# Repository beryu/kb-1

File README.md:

# komoro

komoroは、19mmトラックボールを搭載した左右分割キーボードです。

コンパクトな17mmピッチのカラムスタッカード配列を採用し、左右合わせて48キーを搭載しています。
トラックボールの高さを低く抑えることで、キーを打つときや持ち運びの邪魔になりにくくしています。
コントローラーにはSeeed Studio XIAO nRF52840 Plusを採用しています。XIAOは右側だけに搭載し、左右間はSamtec FTSHヘッダとFFSD-06-D-10.00-01-Nケーブルで接続します。PCとはBluetoothで通信しますが、動作中は右側USB-Cから常に給電する必要があります。

| 左側PCB | 右側PCB |
| --- | --- |
|  |  |

※画像は旧リビジョンの基板です。現行のコネクタや部品配置は[`pcb/`の製造用PCBデータ](pcb/)を確認してください。

## [ビルドガイド](build-guide.md)

## 特徴

* 17mmピッチのカラムスタッカード配列
  * 左26キー、右22キーの48キー構成です。
* USB-C給電・Bluetooth接続
  * PCとの通信にはBluetoothを使用します。
  * 使用中は右側XIAOへモバイルバッテリーまたはUSB電源から常に給電する必要があります。
  * 電源スイッチはなく、USB-Cケーブルの接続／取り外しで電源を操作します。
  * 左右間は、Samtec FFSD-06-D-10.00-01-Nケーブルで接続します。
* Seeed Studio XIAO nRF52840 Plusを採用
  * XIAOは右側だけに搭載し、左側はコントローラーを持たない受動基板です。
* トラックボールの設置位置が調整可能
  * トラックボールを取り付ける位置を調整して、自分にとって一番操作しやすい位置に設置できます。ボールの高さを抑えたことでキーを打つときの邪魔になりにくくなっています。
* ZMK対応
  * [komoro専用ファームウェア](https://github.com/beryu/zmk-keyboard-kb-1)を公開しています。
  * keymap-editorやZMK Studioを使用して簡単にキーマップが変更できます。

## 使用上の注意

* 異臭や煙が出たときは、ただちにUSB-C電源を外して使用を中止してください。
* 左右を接続するFFSDケーブルは、USB-C電源を外した状態で抜き差ししてください。
* USB-C電源とケーブルは、破損や発熱のない適合品を使用してください。

## 設計データについて

本リポジトリでは、komoroの基板設計データと19mmトラックボールケースの設計データを公開しています。

19mmトラックボールケースには、PAW3222センサーモジュールのズレを抑える[ガイド追加版STL](3d-models/STL/trackball-case-19mm-ortho-sensor-fit-Body.stl)を用意しています。寸法と印刷・再生成方法は[センサー溝の調整説明](3d-models/FreeCAD/TRACKBALL-SENSOR-FIT.md)を確認してください。再生成の入力に使う従来版STLは残し、旧トラックボールケースのFreeCADファイルは削除しています。本体ケースのFreeCADデータとSTLは現行PCB外形、左右上面のFFSDコネクタ、右側USB-Cに合わせて更新しています。印刷前に実部品との干渉を確認してください。

ライセンスにしたがって自由に利用していただいて構いませんが、問い合わせには対応しません。

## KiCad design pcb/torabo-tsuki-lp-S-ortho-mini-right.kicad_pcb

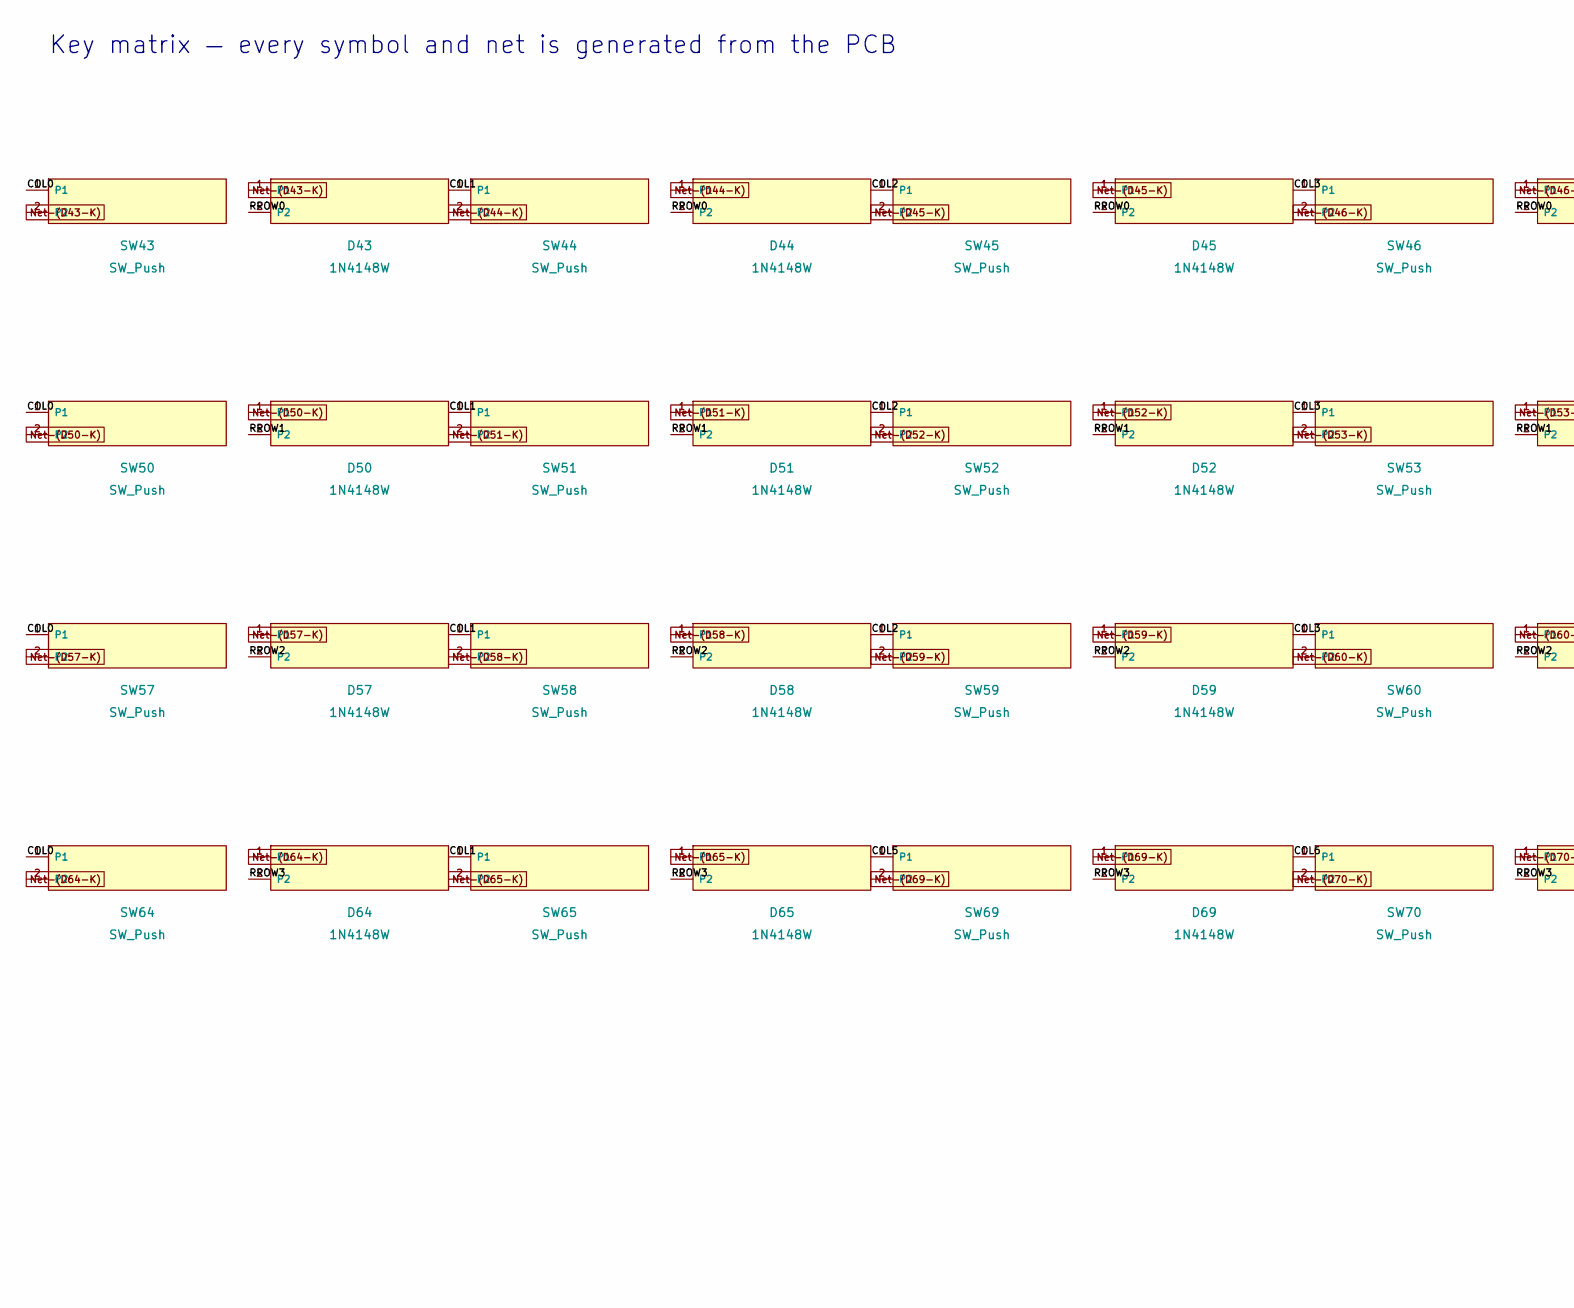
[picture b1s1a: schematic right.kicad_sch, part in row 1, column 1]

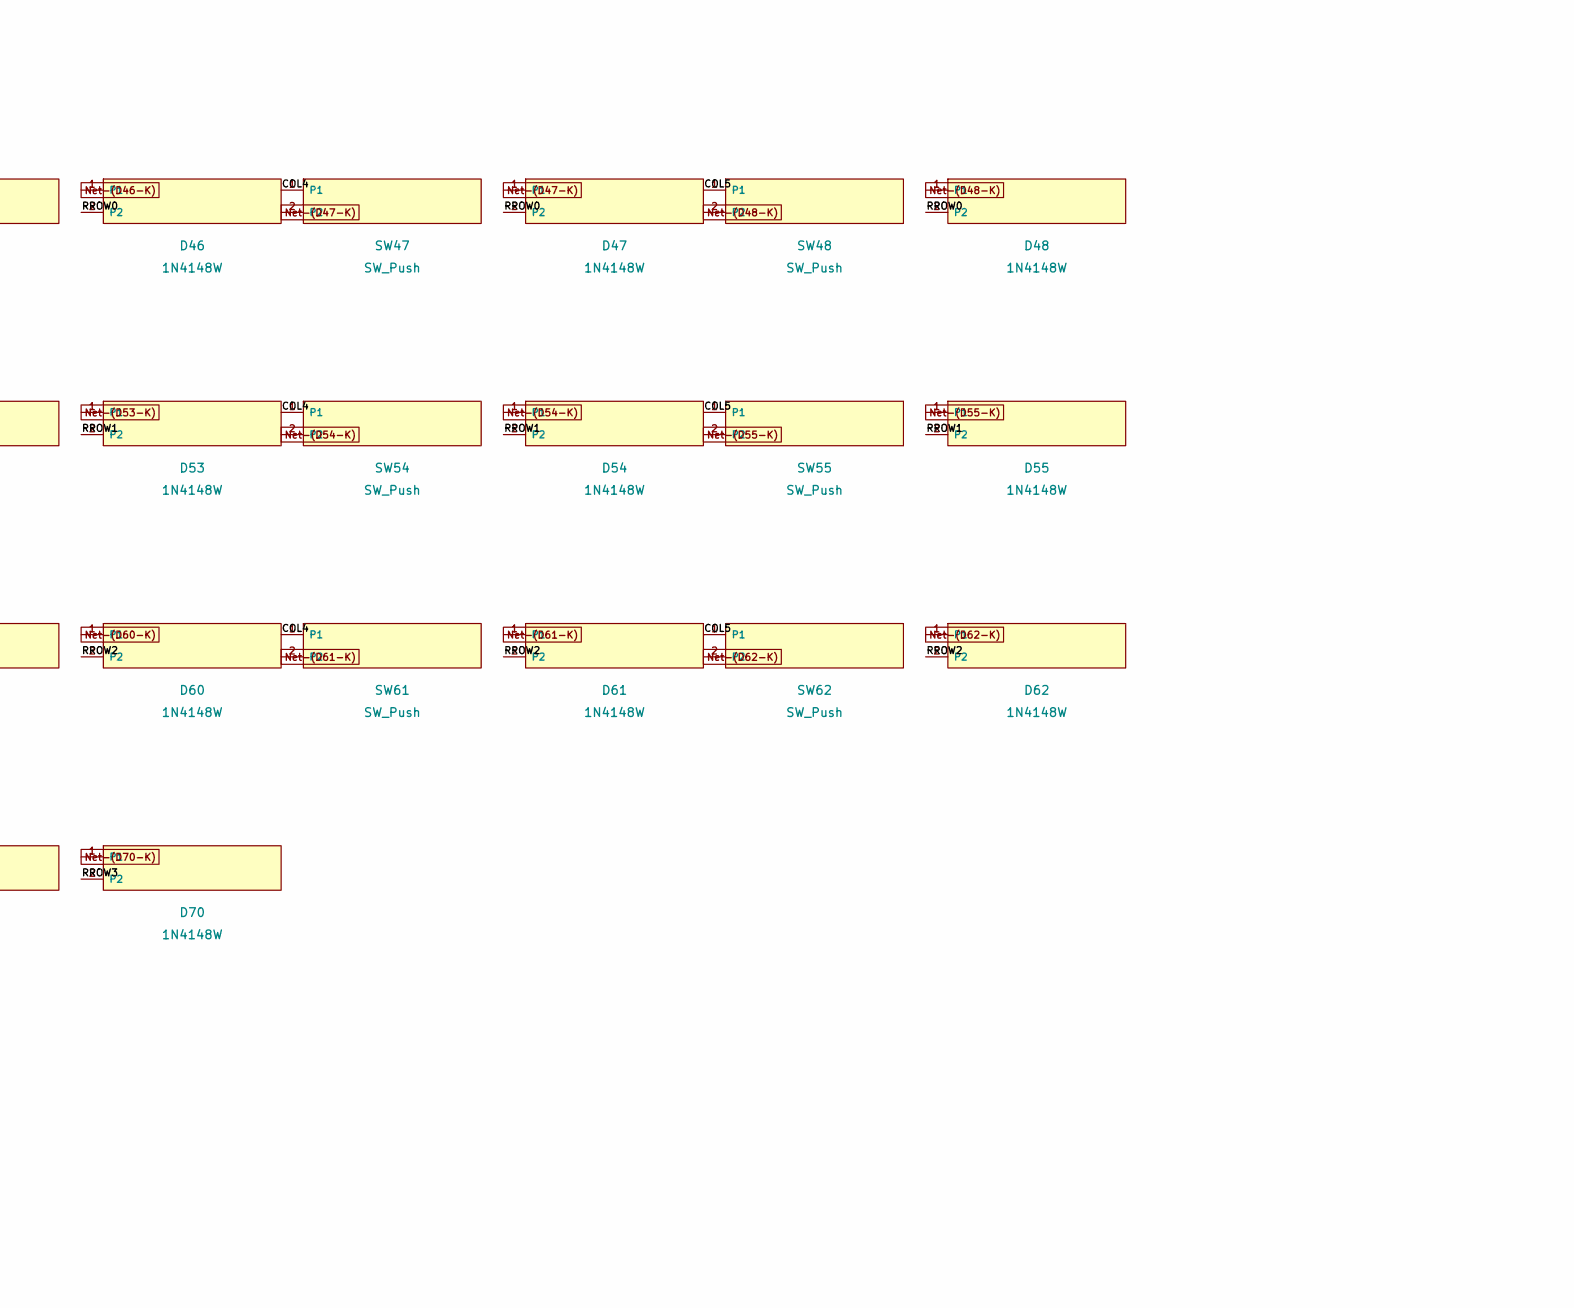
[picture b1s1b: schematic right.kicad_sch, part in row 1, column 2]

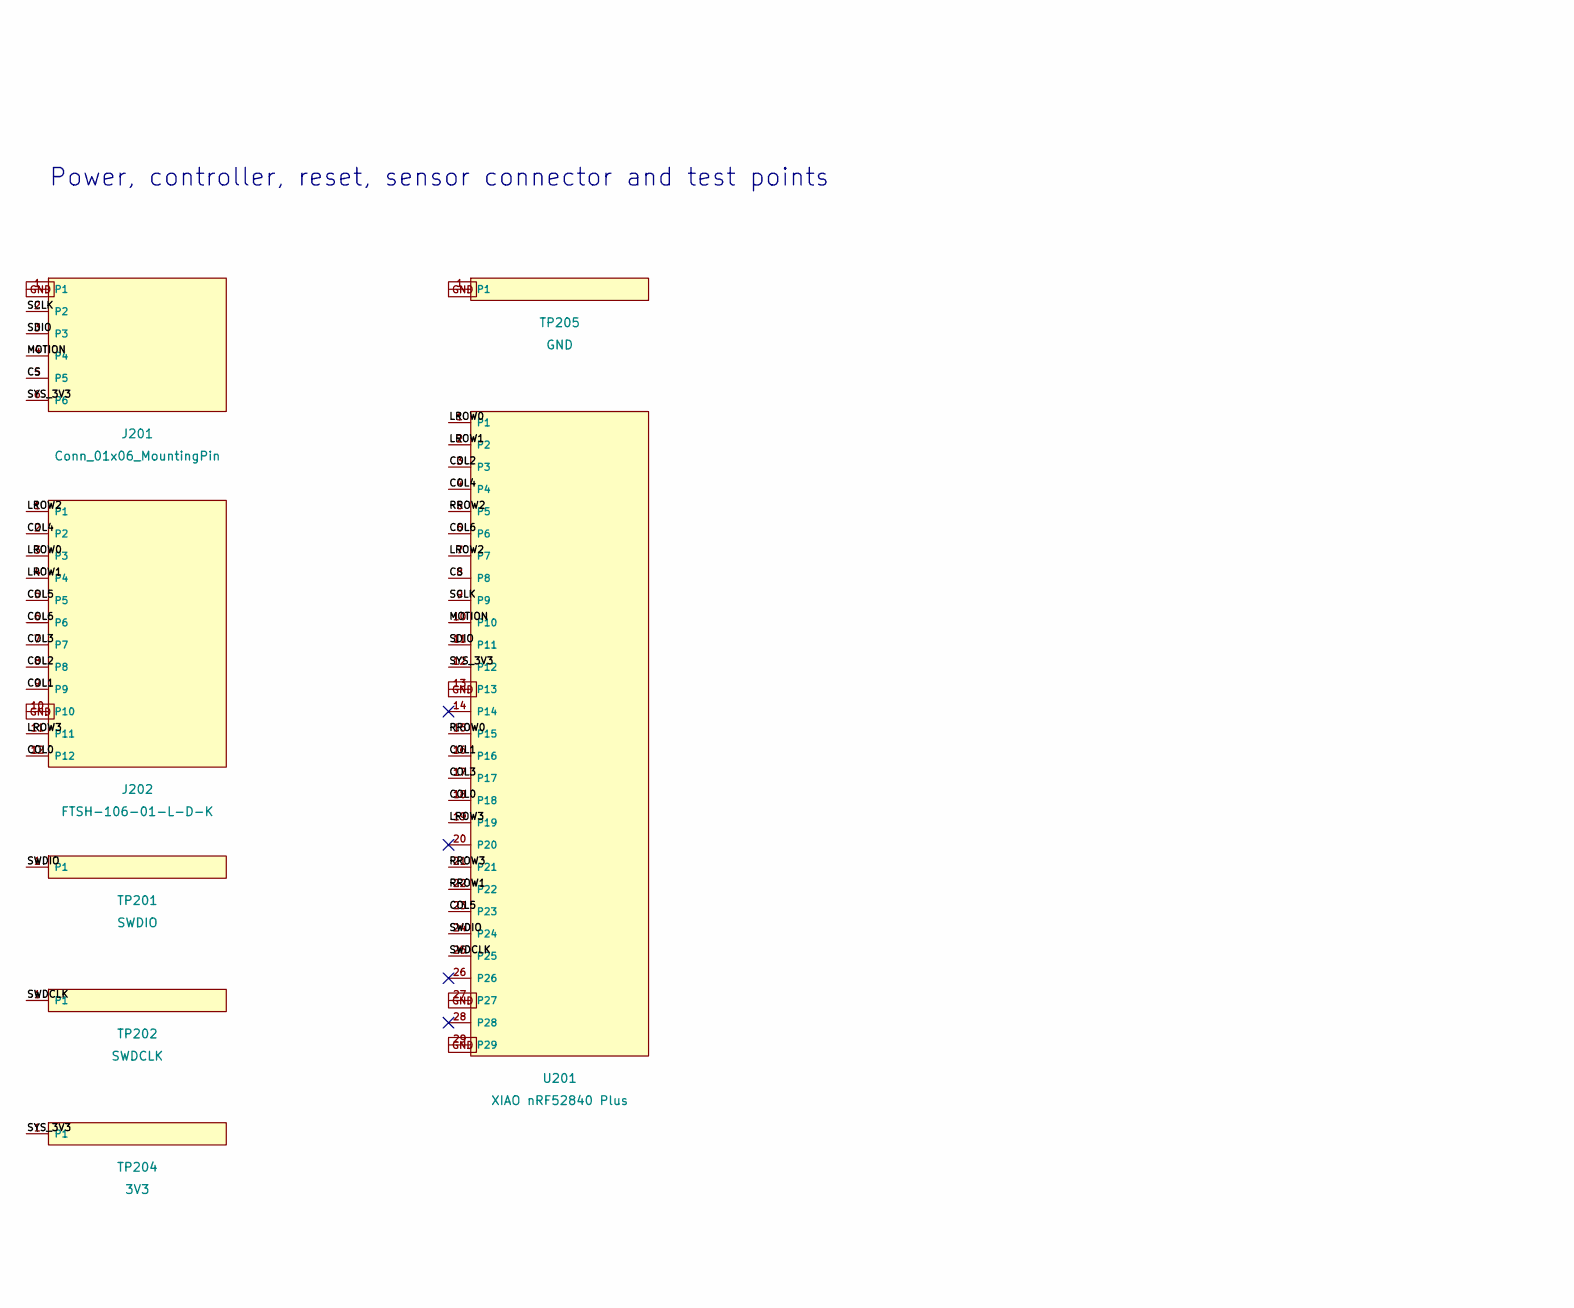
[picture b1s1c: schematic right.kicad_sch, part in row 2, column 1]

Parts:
D43, D44, D45, D46, D47, D48, D50, D51, D52, D53, D54, D55, D57, D58, D59, D60, D61, D62, D64, D65, D69, D70: 1N4148W; D_SOD-123_HandSoldering; MPN 1N4148W; LCSC C81598
J201: Conn_01x06_MountingPin; ffc-6p-adapter
J202: FTSH-106-01-L-D-K; Samtec_FTSH-106-01-L-D-K
SW43, SW44, SW45, SW46, SW47, SW48, SW50, SW51, SW52, SW53, SW54, SW55, SW57, SW58, SW59, SW60, SW61, SW62, SW64, SW65, SW69, SW70: SW_Push; CHOC_V2_SOCKET_HANDSOLDERING_17mm; LCSC C9900009224
TP201: SWDIO; TestPoint_Pad_D1.5mm
TP202: SWDCLK; TestPoint_Pad_D1.5mm
TP204: 3V3; TestPoint_Pad_D1.5mm
TP205: GND; TestPoint_Pad_D1.5mm
U201: XIAO nRF52840 Plus; XIAO-nRF52840-Plus-SMD

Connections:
/right/COL0: J202.12, SW43.1, SW50.1, SW57.1, SW64.1, U201.18
/right/COL1: J202.9, SW44.1, SW51.1, SW58.1, SW65.1, U201.16
/right/COL2: J202.8, SW45.1, SW52.1, SW59.1, U201.3
/right/COL3: J202.7, SW46.1, SW53.1, SW60.1, U201.17
/right/COL4: J202.2, SW47.1, SW54.1, SW61.1, U201.4
/right/COL5: J202.5, SW48.1, SW55.1, SW62.1, SW69.1, U201.23
/right/COL6: J202.6, SW70.1, U201.6
/right/CS: J201.5, U201.8
/right/LROW0: J202.3, U201.1
/right/LROW1: J202.4, U201.2
/right/LROW2: J202.1, U201.7
/right/LROW3: J202.11, U201.19
/right/MOTION: J201.4, U201.10
/right/RROW0: D43.2 (A), D44.2 (A), D45.2 (A), D46.2 (A), D47.2 (A), D48.2 (A), U201.15
/right/RROW1: D50.2 (A), D51.2 (A), D52.2 (A), D53.2 (A), D54.2 (A), D55.2 (A), U201.22
/right/RROW2: D57.2 (A), D58.2 (A), D59.2 (A), D60.2 (A), D61.2 (A), D62.2 (A), U201.5
/right/RROW3: D64.2 (A), D65.2 (A), D69.2 (A), D70.2 (A), U201.21
/right/SCLK: J201.2, U201.9
/right/SDIO: J201.3, U201.11
/right/SWDCLK: TP202.1, U201.25
/right/SWDIO: TP201.1, U201.24
/right/SYS_3V3: J201.6, TP204.1, U201.12
GND: J201.1, J202.10, TP205.1, U201.13, U201.27, U201.29
unnamed: D43.1 (K), SW43.2
unnamed: D44.1 (K), SW44.2
unnamed: D45.1 (K), SW45.2
unnamed: D46.1 (K), SW46.2
unnamed: D47.1 (K), SW47.2
unnamed: D48.1 (K), SW48.2
unnamed: D50.1 (K), SW50.2
unnamed: D51.1 (K), SW51.2
unnamed: D52.1 (K), SW52.2
unnamed: D53.1 (K), SW53.2
unnamed: D54.1 (K), SW54.2
unnamed: D55.1 (K), SW55.2
unnamed: D57.1 (K), SW57.2
unnamed: D58.1 (K), SW58.2
unnamed: D59.1 (K), SW59.2
unnamed: D60.1 (K), SW60.2
unnamed: D61.1 (K), SW61.2
unnamed: D62.1 (K), SW62.2
unnamed: D64.1 (K), SW64.2
unnamed: D65.1 (K), SW65.2
unnamed: D69.1 (K), SW69.2
unnamed: D70.1 (K), SW70.2

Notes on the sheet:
Key matrix — every symbol and net is generated from the PCB
Power, controller, reset, sensor connector and test points
Source of truth: PCB pad/net assignment

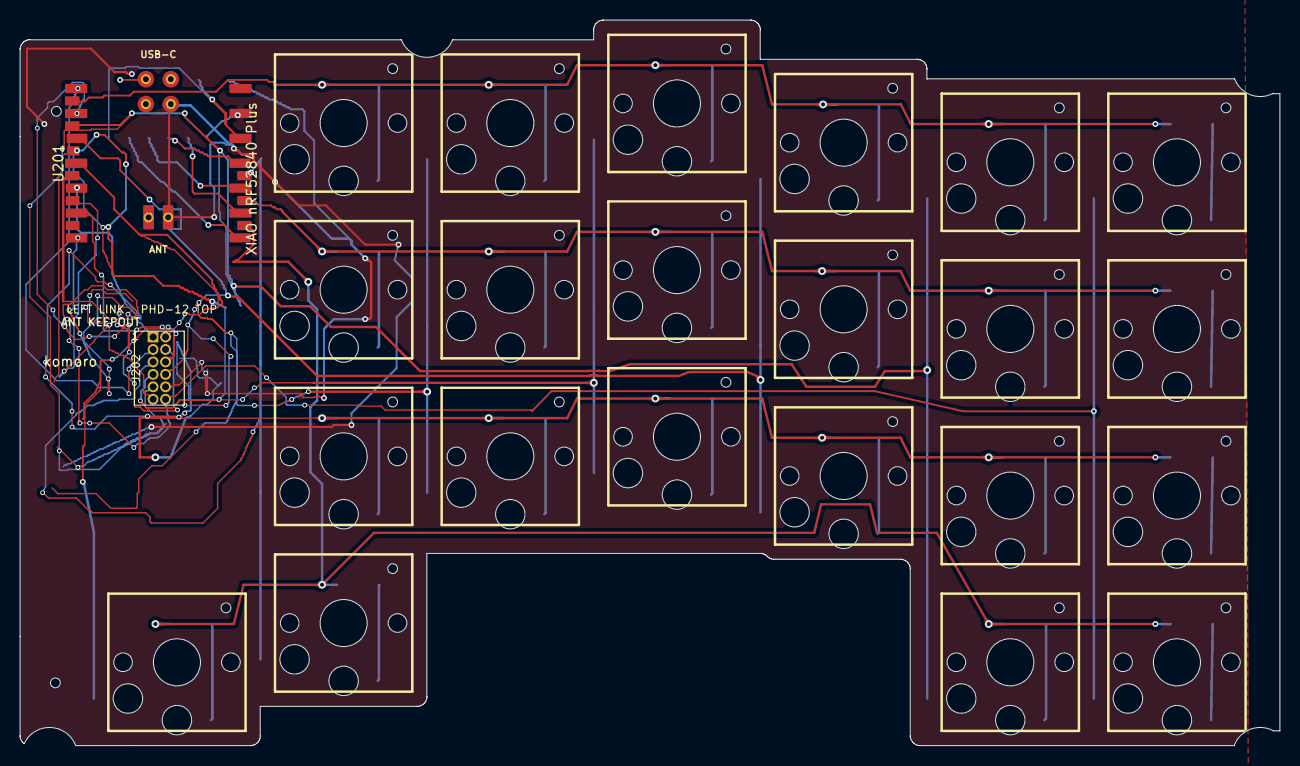
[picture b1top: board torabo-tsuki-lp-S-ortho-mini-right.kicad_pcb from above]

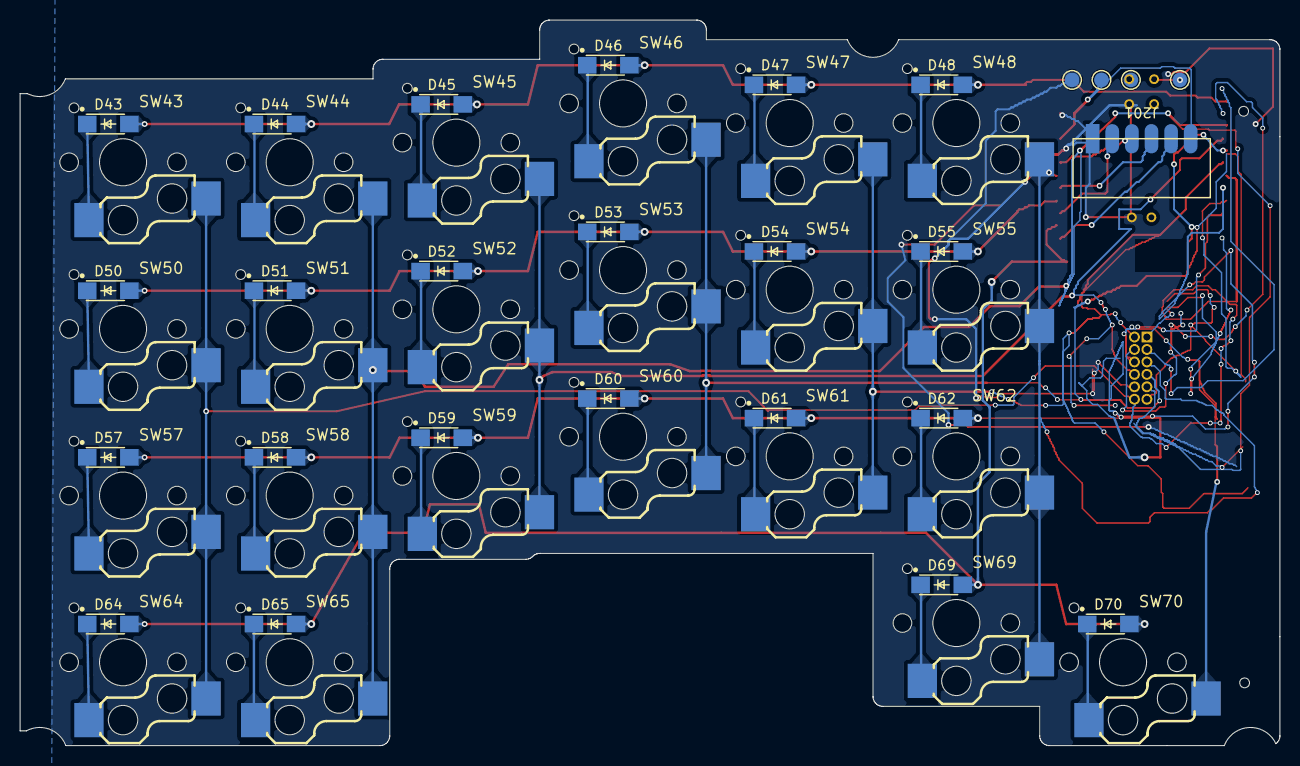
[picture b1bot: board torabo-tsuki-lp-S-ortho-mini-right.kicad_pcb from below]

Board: 2 copper layers, 128.5 x 74.0 mm, 51 parts (49 on the bottom side), 45 nets.

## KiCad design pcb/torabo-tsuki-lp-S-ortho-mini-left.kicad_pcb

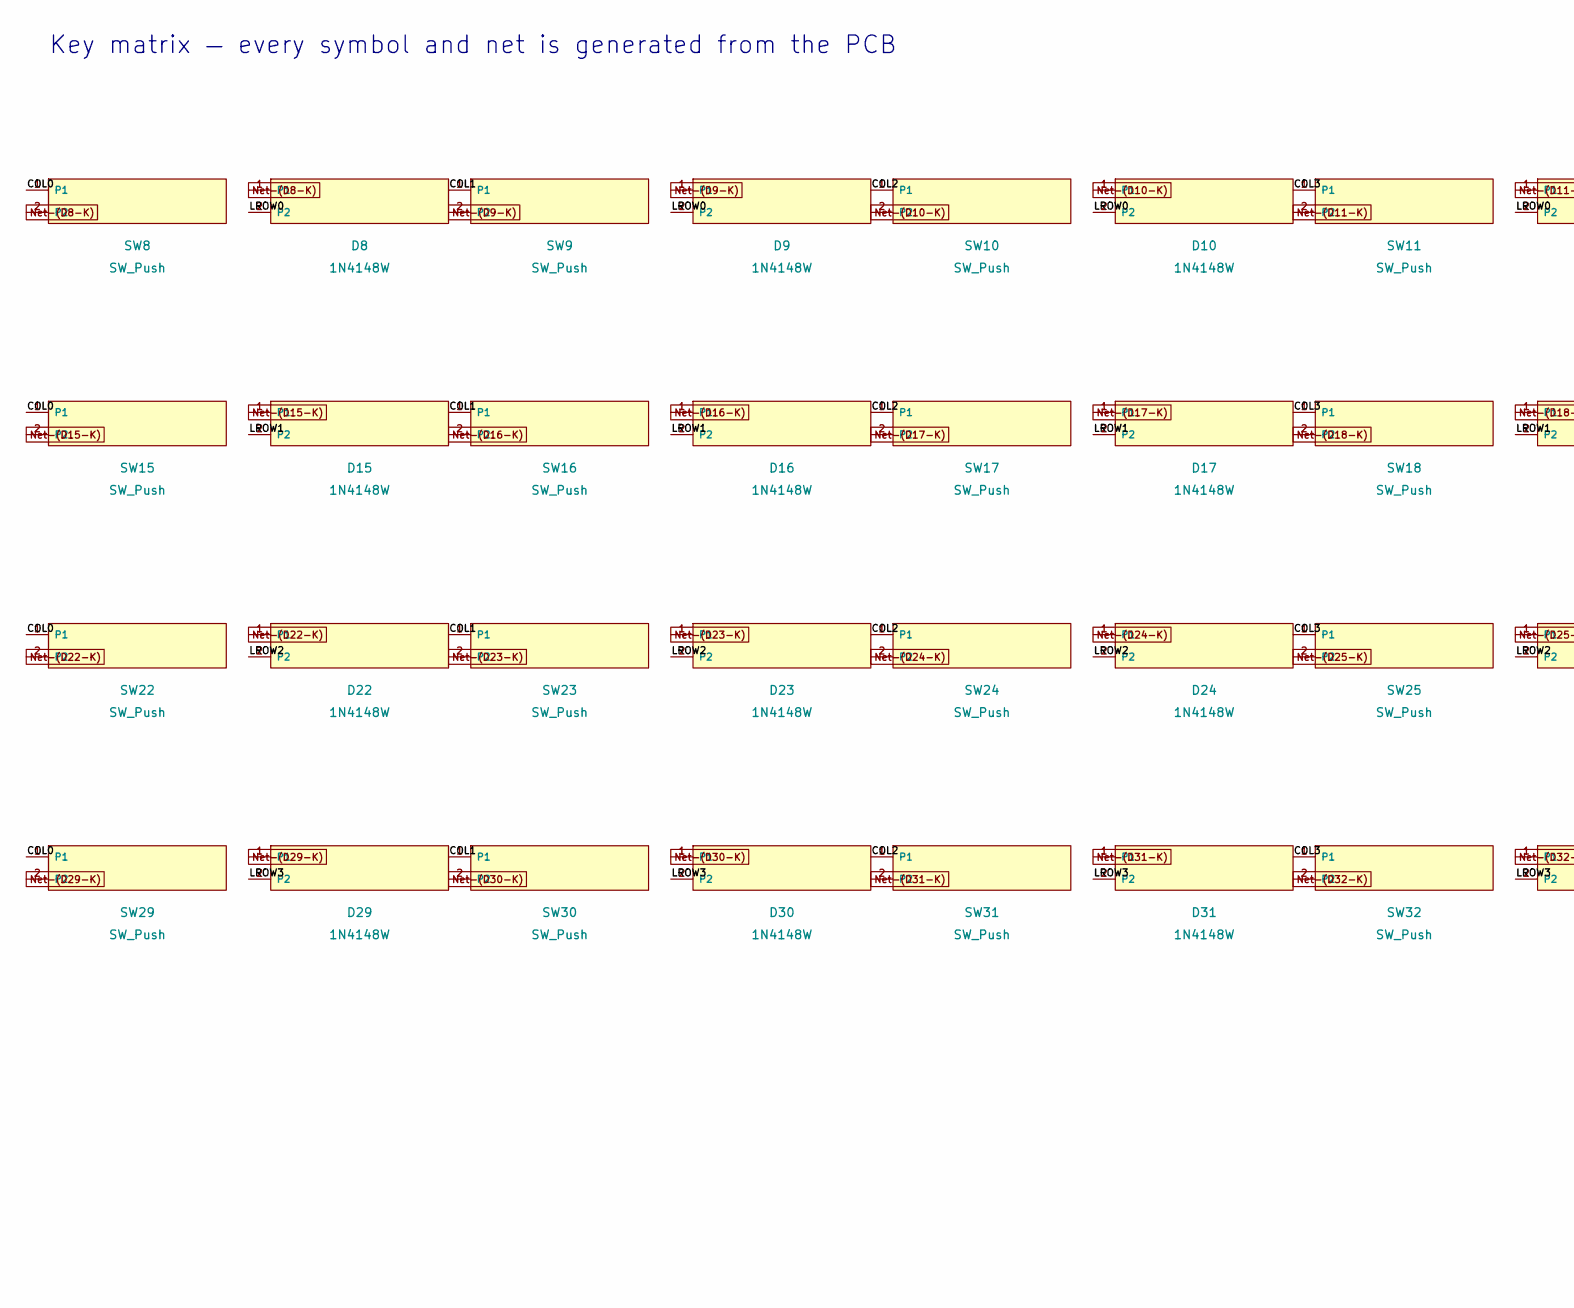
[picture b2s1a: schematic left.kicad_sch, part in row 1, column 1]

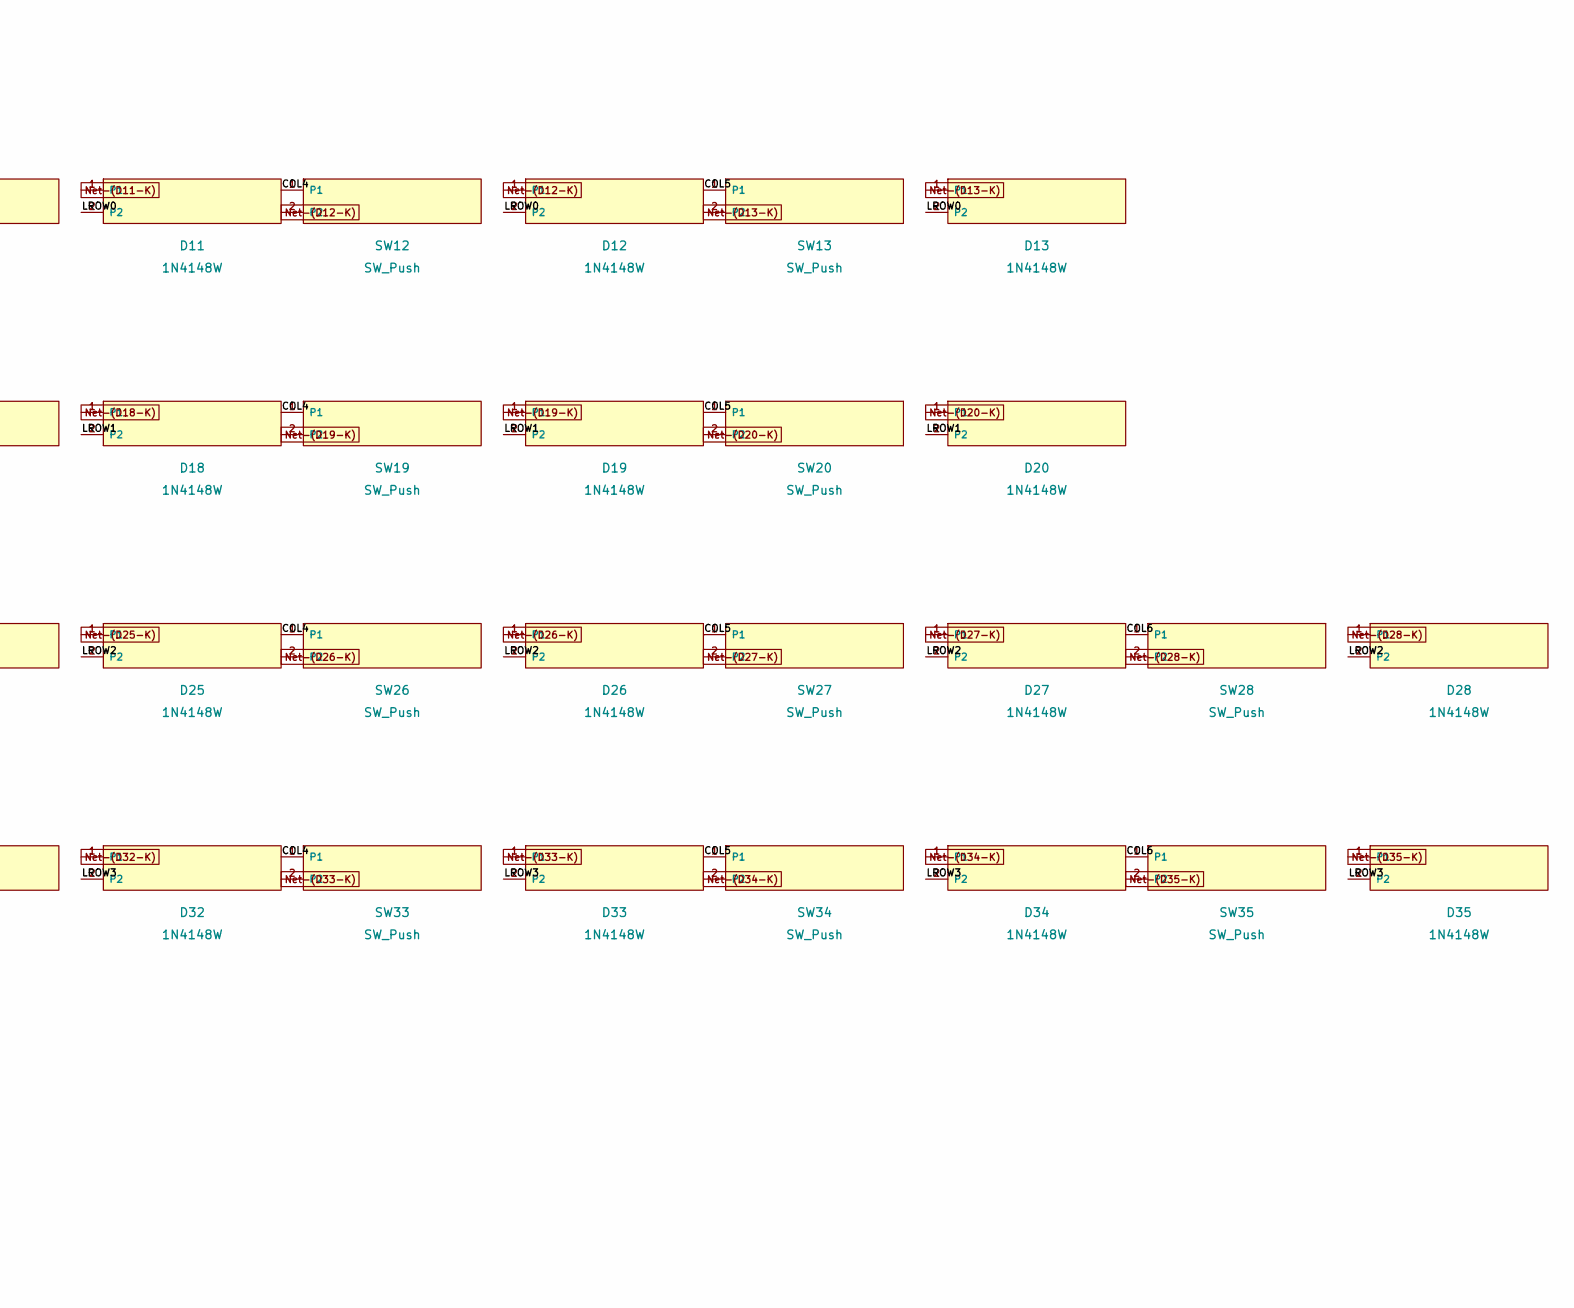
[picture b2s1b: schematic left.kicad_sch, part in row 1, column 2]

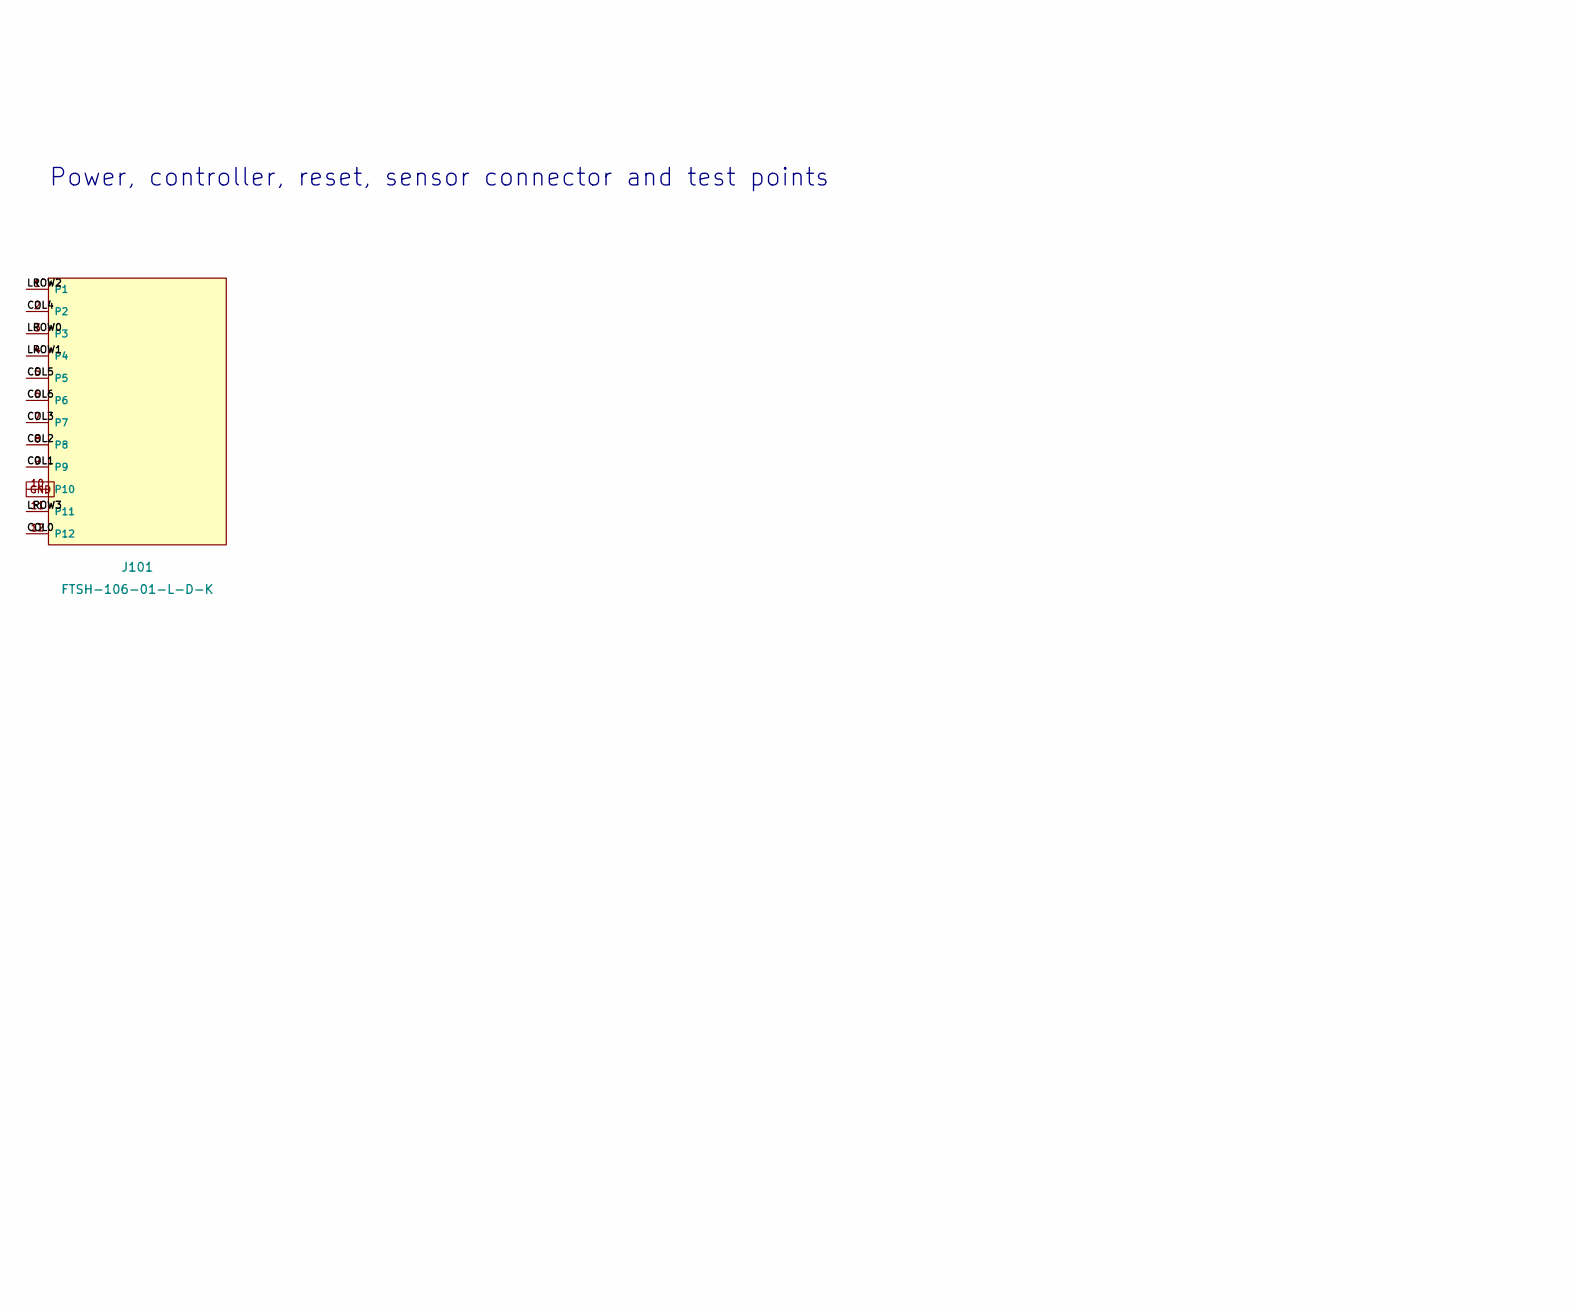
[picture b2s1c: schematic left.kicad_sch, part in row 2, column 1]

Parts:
D8, D9, D10, D11, D12, D13, D15, D16, D17, D18, D19, D20, D22, D23, D24, D25, D26, D27, D28, D29, D30, D31, D32, D33, D34, D35: 1N4148W; D_SOD-123_HandSoldering; MPN 1N4148W; LCSC C81598
J101: FTSH-106-01-L-D-K; Samtec_FTSH-106-01-L-D-K
SW8, SW9, SW10, SW11, SW12, SW13, SW15, SW16, SW17, SW18, SW19, SW20, SW22, SW23, SW24, SW25, SW26, SW27, SW28, SW29, SW30, SW31, SW32, SW33, SW34, SW35: SW_Push; CHOC_V2_SOCKET_HANDSOLDERING_17mm; LCSC C9900009224

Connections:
/left/COL0: J101.12, SW8.1, SW15.1, SW22.1, SW29.1
/left/COL1: J101.9, SW9.1, SW16.1, SW23.1, SW30.1
/left/COL2: J101.8, SW10.1, SW17.1, SW24.1, SW31.1
/left/COL3: J101.7, SW11.1, SW18.1, SW25.1, SW32.1
/left/COL4: J101.2, SW12.1, SW19.1, SW26.1, SW33.1
/left/COL5: J101.5, SW13.1, SW20.1, SW27.1, SW34.1
/left/COL6: J101.6, SW28.1, SW35.1
/left/LROW0: D8.2 (A), D9.2 (A), D10.2 (A), D11.2 (A), D12.2 (A), D13.2 (A), J101.3
/left/LROW1: D15.2 (A), D16.2 (A), D17.2 (A), D18.2 (A), D19.2 (A), D20.2 (A), J101.4
/left/LROW2: D22.2 (A), D23.2 (A), D24.2 (A), D25.2 (A), D26.2 (A), D27.2 (A), D28.2 (A), J101.1
/left/LROW3: D29.2 (A), D30.2 (A), D31.2 (A), D32.2 (A), D33.2 (A), D34.2 (A), D35.2 (A), J101.11
GND: J101.10
unnamed: D8.1 (K), SW8.2
unnamed: D9.1 (K), SW9.2
unnamed: D10.1 (K), SW10.2
unnamed: D11.1 (K), SW11.2
unnamed: D12.1 (K), SW12.2
unnamed: D13.1 (K), SW13.2
unnamed: D15.1 (K), SW15.2
unnamed: D16.1 (K), SW16.2
unnamed: D17.1 (K), SW17.2
unnamed: D18.1 (K), SW18.2
unnamed: D19.1 (K), SW19.2
unnamed: D20.1 (K), SW20.2
unnamed: D22.1 (K), SW22.2
unnamed: D23.1 (K), SW23.2
unnamed: D24.1 (K), SW24.2
unnamed: D25.1 (K), SW25.2
unnamed: D26.1 (K), SW26.2
unnamed: D27.1 (K), SW27.2
unnamed: D28.1 (K), SW28.2
unnamed: D29.1 (K), SW29.2
unnamed: D30.1 (K), SW30.2
unnamed: D31.1 (K), SW31.2
unnamed: D32.1 (K), SW32.2
unnamed: D33.1 (K), SW33.2
unnamed: D34.1 (K), SW34.2
unnamed: D35.1 (K), SW35.2

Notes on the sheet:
Key matrix — every symbol and net is generated from the PCB
Power, controller, reset, sensor connector and test points
Source of truth: PCB pad/net assignment

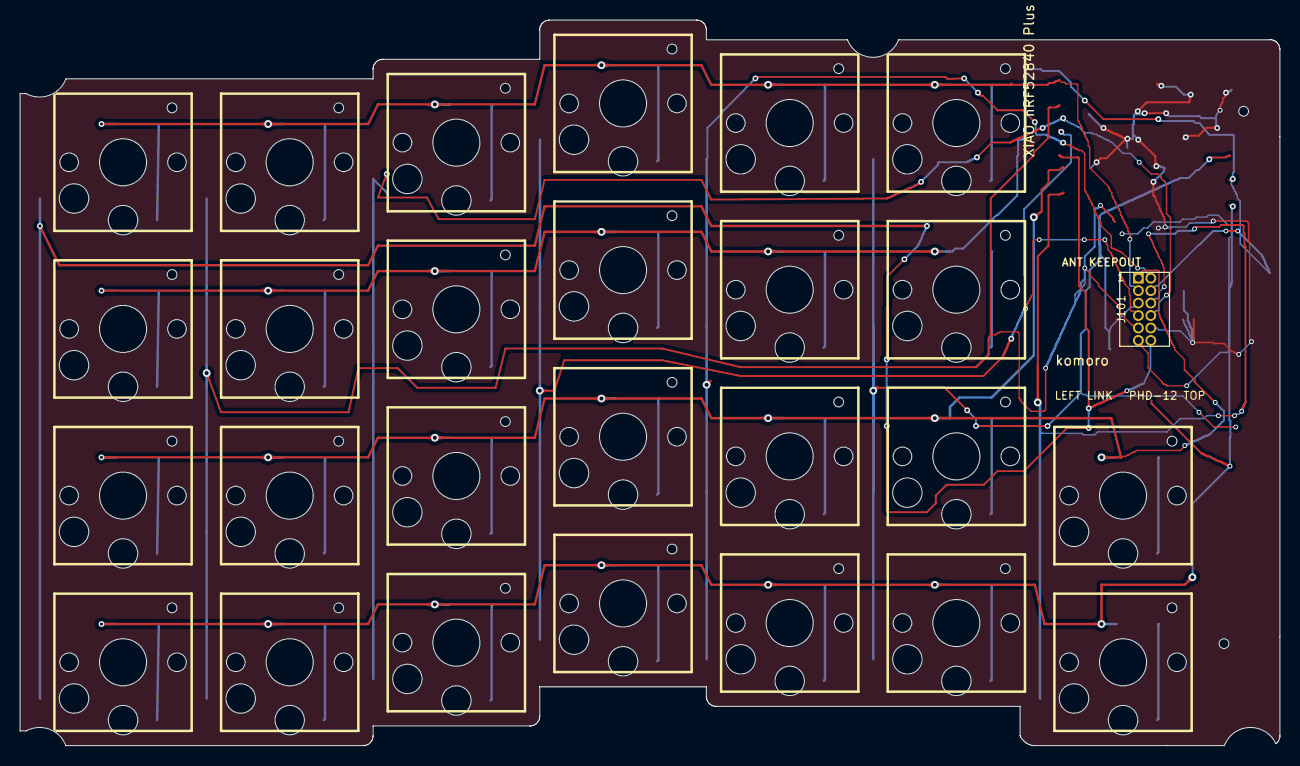
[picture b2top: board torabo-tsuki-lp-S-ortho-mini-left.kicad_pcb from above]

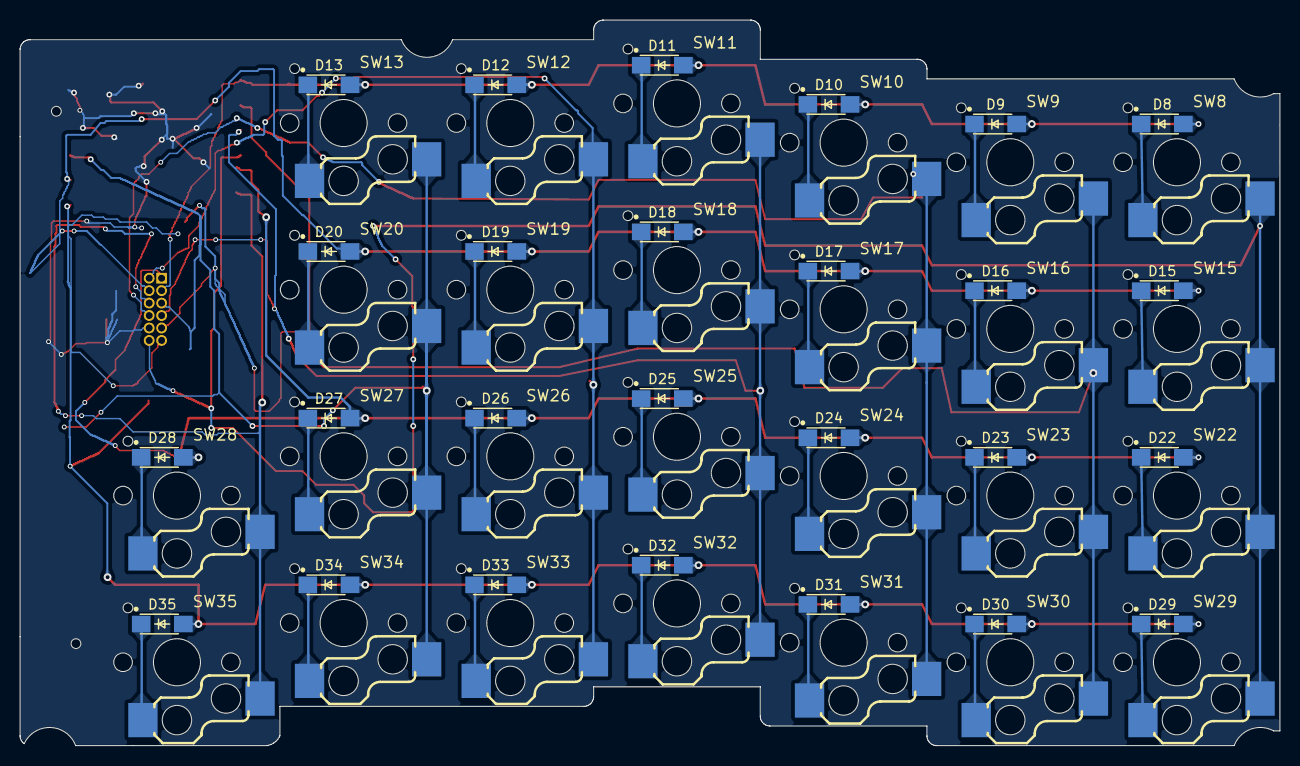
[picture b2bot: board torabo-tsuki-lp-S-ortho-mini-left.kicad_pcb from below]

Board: 2 copper layers, 128.5 x 74.0 mm, 53 parts (52 on the bottom side), 37 nets.

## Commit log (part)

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2025-10-20 Update resistor specification in build guide
2025-10-20 Add SMD diode entry to build guide
2025-10-26 Add a switch socket to the parts list
